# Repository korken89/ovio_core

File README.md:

# Open Visual Inertial Odometry (OVIO) Core

## Current status

Work in progress. PCB have arrived for v1.0 of the board and bring-up has started.

### Issues with v1.0 hardware (fixed in v1.1)

* The MOSFET is 180 degrees rotated.
* The MOSI/MISO lines for the SPI flash are swapped.
* The CS line of the SPI flash is connected to the wrong pad on the FPGA, flashing and loading bitstream from v1.0 hardware will not work.

Images from the assembly and results here: https://twitter.com/korken89/status/1341126909485342721

## Motivation

Aim: A "low cost" Visual Inertial Odometry accelerator.

A project to try out different vision processing pipelines, for Visual Inertial Odometry (VIO), on the ECP5 FPGA. As far as I know, the open hardware landscape of VIO cameras is slim to non-existent. Especially for systems which perform a majority of the pre-processing in the camera.

Things such as image convolutions, FAST corners, multi-scale images, non-maximum suppression, image gradients, etc, are extremely well suited for FPGA implementation.

Why do it on a PC? Let it run the actual Kalman Filter / MHE / nonlinear optimizer, which the FPGA is not well suited for.

## Specs

* Lattice ECP5U-85, design is pin-compatible to all the smaller versions
* 1 GBit DDR3 memory
* FT600 USB 3.0 FIFO with 200 MB/s transfer rate
* 2x MT9V034 cameras with tight hardware synchronization control loops (center of integration of both cameras are aligned to IMU measurements)
* Temperature stabilized ST ISM330DHC IMU (16g / 4000 dps max)

## Do you want one?

Previous projects has been made on Xilinx FPGAs, however the high cost of their FPGAs never allowed for trying to distribute a camera. Now it is expected that the hardware cost for this system should be sub 100 Euros, even with the largest ECP5 FPGA.

If there is interest for acquiring a camera, contact me (via any medium) and we'll figure something out.

## Lenses and lens holder

* http://www.m12lenses.com/2-1mm-F2-2-Board-Lens-p/pt-02120.htm
* http://www.m12lenses.com/M12-Lens-Holder-Plastic-p/pt-lh001p.htm

## Contributors

- Emil Fresk ([@korken89](https://github.com/korken89/))

## License

This hardware is open source.

TODO: Find a proper license

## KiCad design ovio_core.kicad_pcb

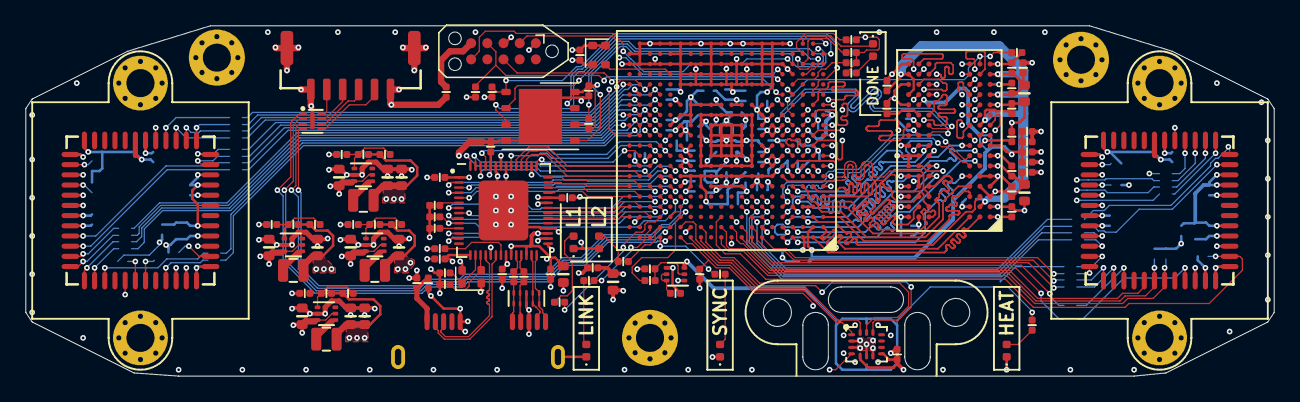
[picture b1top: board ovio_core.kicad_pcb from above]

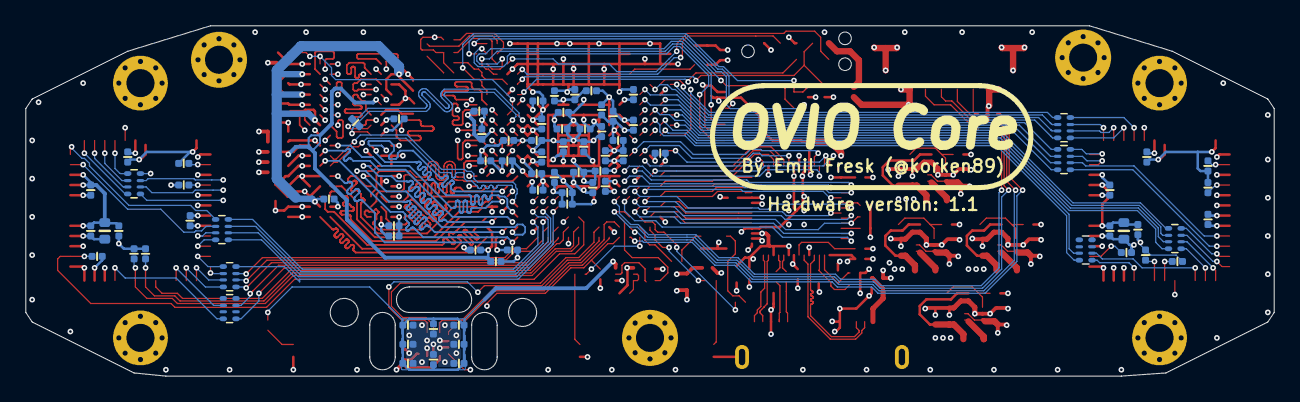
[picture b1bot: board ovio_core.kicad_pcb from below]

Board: 6 copper layers, 98.0 x 27.5 mm, 196 parts (81 on the bottom side), 224 nets.

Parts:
C101, C103, C210, C211, C214, C215, C218, C301, C303, C403, C404, C405, C406, C407, C408, C409, C410, C411, C412, C415, C416, C502, C601, C603, C605, C607, C608, C611, C612, C615, C616, C619, C620, C623, C624, C627, C701, C703, C705, C706, C707, C708, C709, C712, C713, C714, C715: 0.1u; C_0402
C102, C104, C212, C213, C216, C217, C219, C302, C413, C414, C418, C602, C604, C606, C609, C610, C617, C618, C621, C622, C625, C626, C628, C702, C704: 10n; C_0402
C201, C202, C203, C204, C401, C402, C501, C716: 4.7u; C_0603
C205, C206, C207, C208, C209, C220, C613, C614: 22u; C_0603
C221, C222, C223, C224, C710, C711: 10p; C_0402
D101, D102, D103, D104, D301, D501: LED_Small; LED_0402_1005Metric
FB401, FB402, FB501, FB601, FB602, FB701: Ferrite_Bead_Small; R_0402
H101, H102, H103: MountingHole_Pad; MountingHole_2.2mm_M2_Pad_Via
H501, H502: MountingHole; MountingHole_2.2mm_M2
J101: Conn_01x06; SM06B-GHS-TB
J301: TC2050; Tag-Connect_TC2050-IDC-NL_2x05_P1.27mm_Vertical
J701: USB3_B_Micro; AMPHENOL-GSB343K33HR
L201, L202, L203, L204: 2.2u; L_0806_2016Metric
LH401, LH402: lens_holder; m12_20mm
Q501: NTZD3155C; SOT-563
R101, R102, R103, R104, R301, R302, R303, R304, R306, R407, R408, R409, R410, R513, R601, R602: 1k; R_0402
R201, R204: 100k; R_0402
R202: 120k; R_0402
R203: 150k; R_0402
R205: 261k; R_0402
R206, R208: 82k; R_0402
R207: 365k; R_0402
R305, R307, R403, R404, R502, R503, R508, R604, R701, R702, R703: 10k; R_0402
R308: 0; R_0402
R401, R402, R405, R406, R704: 1.6k; R_0402
R501, R504, R505, R506, R507, R509, R510, R511, R512: 180; R_0402
R603: 100; R_0402
R605: 240; R_0402
RN401, RN402, RN403, RN404, RN406, RN407, RN408, RN409: 22; R_Array_Convex_4x0402
U101: IP4254CZ8-4-TTL; UDFN-8-1EP_1.7x1.35mm_P0.4mm_EP0.4x1.2mm
U102: ECP5U_85_CABGA381; caBGA_381_17x17
U201, U202, U203, U204: TLV62569DRL; SOT-563
U302: W25Q128JVP; WSON-8-1EP_6x5mm_P1.27mm_EP3.4x4.3mm
U401, U402: MT9V034
U403: 25 MHz; Crystal_4Pin_2.0x1.6mm
U501: ISM330DHC; LGA-14-2.5x3
U601: MT41J128M16JT-125:K; BGA-96_8.0x14.0mm_DDR16
U701: FT600Q; QFN-56-1EP_7x7mm_P0.4mm_EP5.7x5.7mm_FT600
U702: PUSB3FR4Z; DFN-10-1.0x2.5mm_P0.5mm
Y701: 30 MHz; Crystal_4Pin_2.0x1.6mm

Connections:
+1V1: C205.1, C209.1, C210.1, C212.1, C214.1, C216.1, C218.1, C219.1, C221.2, L201.2, R201.2, U102.H8, U102.H9, U102.H10, U102.H11, U102.H12, U102.H13, U102.J8, U102.J13, U102.K8, U102.K13, U102.L8, U102.L13, U102.M8, U102.M13, U102.N8, U102.N9, U102.N10, U102.N11, U102.N12, U102.N13
+1V5: C206.1, C222.2, C601.1, C602.1, C603.1, C604.1, C605.1, C606.1, C611.1, C627.1, C628.1, FB601.1, FB602.1, L202.2, R203.2, R601.1, U102.A3, U102.D2, U102.D3, U102.H3, U102.H6, U102.H7, U102.J5, U102.J6, U102.L3, U102.L6, U102.L7, U102.M5, U102.M6, U102.N1
+2V5: C207.1, C211.1, C213.1, C215.1, C217.1, C223.2, L203.2, R205.2, U102.F6, U102.F15, U102.P6, U102.P15
+3V3: C101.1, C102.1, C103.1, C104.1, C208.1, C220.1, C224.2, C301.1, C302.1, C303.1, C403.1, C405.1, C407.1, C409.1, C411.1, C412.1, C413.1, C414.1, C415.1, C416.1, C418.1, C701.1, C702.1, C703.1, C704.1, C706.1, C707.1, C708.1, C714.1, FB401.2, FB402.2, FB501.2, J301.1, L204.2, R207.2, R301.1, R302.1, R303.1, R304.1, R305.1, R307.1, R401.2, R402.2, R405.2, R406.2, R407.1, R408.1, R409.1, R410.1, R701.1, R702.1, R703.1, U102.F9, U102.F10, U102.F11, U102.F12, U102.H14, U102.H15, U102.J15, U102.J18, U102.L14, U102.L15, U102.M15, U102.P9, U102.P10, U302.8, U401.1, U401.6, U401.14, U401.28, U402.1, U402.6, U402.14, U402.28, U403.1, U403.4, U701.15, U701.19, U701.22, U701.30, U701.38, U701.44, U701.52
+5V: C201.1, C202.1, C203.1, C204.1, FB701.1, J101.1, Q501.4, R308.2, R503.1, U201.3, U201.5, U202.3, U202.5, U203.3, U203.5, U204.3, U204.5, U701.29
/2x cameras & FPGA Clock/CAM0_D0: RN402.7, U102.E8
/2x cameras & FPGA Clock/CAM0_D0_P: RN402.2, U401.45
/2x cameras & FPGA Clock/CAM0_D1: RN402.6, U102.E9
/2x cameras & FPGA Clock/CAM0_D1_P: RN402.3, U401.44
/2x cameras & FPGA Clock/CAM0_D2: RN402.5, U102.C10
/2x cameras & FPGA Clock/CAM0_D2_P: RN402.4, U401.43
/2x cameras & FPGA Clock/CAM0_D3: RN403.8, U102.C7
/2x cameras & FPGA Clock/CAM0_D3_P: RN403.1, U401.42
/2x cameras & FPGA Clock/CAM0_D4: RN403.7, U102.C8
/2x cameras & FPGA Clock/CAM0_D4_P: RN403.2, U401.41
/2x cameras & FPGA Clock/CAM0_D5: RN403.6, U102.D7
/2x cameras & FPGA Clock/CAM0_D5_P: RN403.3, U401.15
/2x cameras & FPGA Clock/CAM0_D6: RN403.5, U102.D8
/2x cameras & FPGA Clock/CAM0_D6_P: RN403.4, U401.16
/2x cameras & FPGA Clock/CAM0_D7: RN404.8, U102.D9
/2x cameras & FPGA Clock/CAM0_D7_P: RN404.1, U401.17
/2x cameras & FPGA Clock/CAM0_D8: RN404.7, U102.A7
/2x cameras & FPGA Clock/CAM0_D8_P: RN404.2, U401.18
/2x cameras & FPGA Clock/CAM0_D9: RN404.6, U102.B8
/2x cameras & FPGA Clock/CAM0_D9_P: RN404.3, U401.19
/2x cameras & FPGA Clock/CAM0_FLASH: RN401.1, U102.A9
/2x cameras & FPGA Clock/CAM0_FLASH_P: RN401.8, U401.27
/2x cameras & FPGA Clock/CAM0_FV: RN401.3, U102.B9
/2x cameras & FPGA Clock/CAM0_FV_P: RN401.6, U401.21
/2x cameras & FPGA Clock/CAM0_LV: RN404.5, U102.A8
/2x cameras & FPGA Clock/CAM0_LV_P: RN404.4, U401.20
/2x cameras & FPGA Clock/CAM0_PIXCLK: RN402.8, U102.A10
/2x cameras & FPGA Clock/CAM0_PIXCLK_P: RN402.1, U401.46
/2x cameras & FPGA Clock/CAM0_RESET: R403.1, U102.C11, U401.32
/2x cameras & FPGA Clock/CAM0_SCLK: R405.1, U102.A11, U401.25
/2x cameras & FPGA Clock/CAM0_SDATA: R401.1, U102.B11, U401.24
/2x cameras & FPGA Clock/CAM0_SYSCLK: U102.E7, U401.47
/2x cameras & FPGA Clock/CAM0_TRIGGER: U102.B10, U401.23
/2x cameras & FPGA Clock/CAM0_VAA: C401.1, C404.1, C408.1, FB401.1, U401.35, U401.39, U401.40
/2x cameras & FPGA Clock/CAM1_D0: RN407.8, U102.T18
/2x cameras & FPGA Clock/CAM1_D0_P: RN407.1, U402.45
/2x cameras & FPGA Clock/CAM1_D1: RN407.7, U102.T20
/2x cameras & FPGA Clock/CAM1_D1_P: RN407.2, U402.44
/2x cameras & FPGA Clock/CAM1_D2: RN407.6, U102.T19
/2x cameras & FPGA Clock/CAM1_D2_P: RN407.3, U402.43
/2x cameras & FPGA Clock/CAM1_D3: RN408.5, U102.R17
/2x cameras & FPGA Clock/CAM1_D3_P: RN408.4, U402.42
/2x cameras & FPGA Clock/CAM1_D4: RN408.6, U102.P19
/2x cameras & FPGA Clock/CAM1_D4_P: RN408.3, U402.41
/2x cameras & FPGA Clock/CAM1_D5: RN408.7, U102.P17
/2x cameras & FPGA Clock/CAM1_D5_P: RN408.2, U402.15
/2x cameras & FPGA Clock/CAM1_D6: RN408.8, U102.N19
/2x cameras & FPGA Clock/CAM1_D6_P: RN408.1, U402.16
/2x cameras & FPGA Clock/CAM1_D7: RN409.5, U102.N20
/2x cameras & FPGA Clock/CAM1_D7_P: RN409.4, U402.17
/2x cameras & FPGA Clock/CAM1_D8: RN409.6, U102.N18
/2x cameras & FPGA Clock/CAM1_D8_P: RN409.3, U402.18
/2x cameras & FPGA Clock/CAM1_D9: RN409.7, U102.M20
/2x cameras & FPGA Clock/CAM1_D9_P: RN409.2, U402.19
/2x cameras & FPGA Clock/CAM1_FLASH: RN406.4, U102.M18
/2x cameras & FPGA Clock/CAM1_FLASH_P: RN406.5, U402.27
/2x cameras & FPGA Clock/CAM1_FV: RN406.3, U102.L19
/2x cameras & FPGA Clock/CAM1_FV_P: RN406.6, U402.21
/2x cameras & FPGA Clock/CAM1_LV: RN409.8, U102.M19
/2x cameras & FPGA Clock/CAM1_LV_P: RN409.1, U402.20
/2x cameras & FPGA Clock/CAM1_PIXCLK: RN407.5, U102.L20
/2x cameras & FPGA Clock/CAM1_PIXCLK_P: RN407.4, U402.46
/2x cameras & FPGA Clock/CAM1_RESET: R404.1, U102.L17, U402.32
/2x cameras & FPGA Clock/CAM1_SCLK: R406.1, U102.L18, U402.25
/2x cameras & FPGA Clock/CAM1_SDATA: R402.1, U102.M17, U402.24
/2x cameras & FPGA Clock/CAM1_SYSCLK: U102.N17, U402.47
/2x cameras & FPGA Clock/CAM1_TRIGGER: U102.L16, U402.23
/2x cameras & FPGA Clock/CAM1_VAA: C402.1, C406.1, C410.1, FB402.1, U402.35, U402.39, U402.40
/2x cameras & FPGA Clock/CLOCK_PLL_IN: U102.U16, U403.3
/DDR3 Memory/A0: U102.K2, U601.N3
/DDR3 Memory/A1: U102.L4, U601.P7
/DDR3 Memory/A2: U102.L2, U601.P3
/DDR3 Memory/A3: U102.J1, U601.N2
/DDR3 Memory/A4: U102.N2, U601.P8
/DDR3 Memory/A5: U102.L1, U601.P2
/DDR3 Memory/A6: U102.P2, U601.R8
/DDR3 Memory/A7: U102.P1, U601.R2
/DDR3 Memory/A8: U102.M3, U601.T8
/DDR3 Memory/A9: U102.L5, U601.R3
/DDR3 Memory/A10: U102.K1, U601.L7
/DDR3 Memory/A11: U102.N3, U601.R7
/DDR3 Memory/A12: U102.K3, U601.N7
/DDR3 Memory/A13: U102.P5, U601.T3
/DDR3 Memory/BA0: U102.H1, U601.M2
/DDR3 Memory/BA1: U102.M1, U601.N8
/DDR3 Memory/BA2: U102.K4, U601.M3
/DDR3 Memory/CAS_N: U102.G1, U601.K3
/DDR3 Memory/CK_E: U102.J3, U601.K9
/DDR3 Memory/CK_N: R603.2, U102.N5, U601.K7
/DDR3 Memory/CK_P: R603.1, U102.M4, U601.J7
/DDR3 Memory/CS_N: U102.H2, U601.L2
/DDR3 Memory/DQ0: U102.A4, U601.E3
/DDR3 Memory/DQ1: U102.C3, U601.F7
/DDR3 Memory/DQ2: U102.A5, U601.F2
/DDR3 Memory/DQ3: U102.B5, U601.F8
/DDR3 Memory/DQ4: U102.E3, U601.H3
/DDR3 Memory/DQ5: U102.F4, U601.H8
/DDR3 Memory/DQ6: U102.C4, U601.G2
/DDR3 Memory/DQ7: U102.C5, U601.H7
/DDR3 Memory/DQ8: U102.D1, U601.D7
/DDR3 Memory/DQ9: U102.C1, U601.C3
/DDR3 Memory/DQ10: U102.F2, U601.C8
/DDR3 Memory/DQ11: U102.C2, U601.C2
/DDR3 Memory/DQ12: U102.E2, U601.A7
/DDR3 Memory/DQ13: U102.A2, U601.A2
/DDR3 Memory/DQ14: U102.E1, U601.B8
/DDR3 Memory/DQ15: U102.B1, U601.A3
/DDR3 Memory/DRAM_VDD: C613.1, C615.1, C617.1, C619.1, C621.1, C623.1, C625.1, FB601.2, U601.B2, U601.D9, U601.G7, U601.K2, U601.K8, U601.N1, U601.N9, U601.R1, U601.R9
/DDR3 Memory/DRAM_VDDQ: C614.1, C616.1, C618.1, C620.1, C622.1, C624.1, C626.1, FB602.2, U601.A1, U601.A8, U601.C1, U601.C9, U601.D2, U601.E9, U601.F1, U601.H2, U601.H9
/DDR3 Memory/LDM: U102.B4, U601.E7
/DDR3 Memory/LDQS_N: U102.D5, U601.G3
/DDR3 Memory/LDQS_P: U102.E4, U601.F3
/DDR3 Memory/ODT: U102.F1, U601.K1
/DDR3 Memory/RAS_N: U102.G2, U601.J3
/DDR3 Memory/RESET_N: R604.1, U102.N4, U601.T2
/DDR3 Memory/UDM: U102.F3, U601.D3
/DDR3 Memory/UDQS_N: U102.G5, U601.B7
/DDR3 Memory/UDQS_P: U102.H4, U601.C7
/DDR3 Memory/VREF: C607.1, C608.1, C609.1, C610.1, C611.2, C612.1, R601.2, R602.1, U102.B2, U102.K5, U601.H1, U601.M8
/DDR3 Memory/WE_N: U102.J4, U601.L3
/DDR3 Memory/ZQ: R605.1, U601.L8
/FPGA Config/CFG_1: R302.2, U102.T4
/FPGA Config/DONE: D301.1, U102.Y3
/FPGA Config/INITN: R305.2, U102.V3
/FPGA Config/PROGRAMN: R304.2, U102.W3
/FPGA Config/SPI_CLK: R301.2, U102.U3, U302.6
/FPGA Config/SPI_CS: R307.2, U102.R2, U302.1
/FPGA Config/SPI_D2: U102.Y2, U302.3
/FPGA Config/SPI_D3: U102.W1, U302.7
/FPGA Config/SPI_MISO: U102.V2, U302.2
/FPGA Config/SPI_MOSI: U102.W2, U302.5
/FPGA Config/TCK: J301.4, R306.1, U102.T5
/FPGA Config/TDI: J301.8, U102.R5
/FPGA Config/TDO: J301.6, U102.V4
/FPGA Config/TMS: J301.2, U102.U5
/Heated IMU/HEATER_BASE: Q501.5, Q501.6, R503.2
/Heated IMU/HEATER_SIG: Q501.2, R501.1, R502.1
/Heated IMU/IMU_HEATER: Q501.3, R504.1, R505.1, R506.1, R507.1, R509.1, R510.1, R511.1, R512.1, R513.1
/Heated IMU/IMU_PWR: C501.1, C502.1, FB501.1, U501.5, U501.8
/IMU_CS: U102.A13, U501.12
/IMU_HEATER: R501.2, U102.C15
/IMU_INT: R508.1, U102.A15, U501.4
/IMU_SCK: U102.B13, U501.13
/IMU_SDI: U102.B15, U501.14
/IMU_SDO: U102.A14, U501.1
/LED1: R101.1, U102.B17
/LED2: R102.1, U102.C17
/LED3: R103.1, U102.A17
/LED4: R104.1, U102.B18
/P_USER_FLASH_OUT: U101.4, U102.E15
/P_USER_GPIO0: U101.1, U102.A16
/P_USER_GPIO1: U101.2, U102.B16
/P_USER_GPIO2: U101.3, U102.C16
/System Power/FB_1V1: C221.1, R201.1, R202.2, U201.1
/System Power/FB_1V5: C222.1, R203.1, R204.2, U202.1
/System Power/FB_2V5: C223.1, R205.1, R206.2, U203.1
/System Power/FB_3V3: C224.1, R207.1, R208.2, U204.1
/USB FIFO Interface/D_N: J701.2, U701.20
/USB FIFO Interface/D_P: J701.3, U701.18
/USB FIFO Interface/FT_BE0: U102.H17, U701.2
/USB FIFO Interface/FT_BE1: U102.G16, U701.3
/USB FIFO Interface/FT_CLKOUT: U102.J19, U701.43
/USB FIFO Interface/FT_D0: U102.C20, U701.33
/USB FIFO Interface/FT_D1: U102.C18, U701.34
/USB FIFO Interface/FT_D2: U102.D20, U701.35
/USB FIFO Interface/FT_D3: U102.D19, U701.36
/USB FIFO Interface/FT_D4: U102.E20, U701.39
/USB FIFO Interface/FT_D5: U102.E19, U701.40
/USB FIFO Interface/FT_D6: U102.F20, U701.41
/USB FIFO Interface/FT_D7: U102.F19, U701.42
/USB FIFO Interface/FT_D8: U102.G20, U701.45
/USB FIFO Interface/FT_D9: U102.G19, U701.46
/USB FIFO Interface/FT_D10: U102.H20, U701.47
/USB FIFO Interface/FT_D11: U102.J17, U701.48
/USB FIFO Interface/FT_D12: U102.J16, U701.53
/USB FIFO Interface/FT_D13: U102.H16, U701.54
/USB FIFO Interface/FT_D14: U102.H18, U701.55
/USB FIFO Interface/FT_D15: U102.G18, U701.56
/USB FIFO Interface/FT_GPIO0: U102.D17, U701.12
/USB FIFO Interface/FT_GPIO1: U102.E16, U701.13
/USB FIFO Interface/FT_REF: R704.1, U701.21
/USB FIFO Interface/FT_WAKEUP: R701.2, U701.11
/USB FIFO Interface/RX_N: J701.9, U701.27, U702.4, U702.7
/USB FIFO Interface/RX_P: J701.10, U701.28, U702.5, U702.6
/USB FIFO Interface/TX_N: C712.1, J701.6, U702.1, U702.10
/USB FIFO Interface/TX_P: C713.1, J701.7, U702.2, U702.9
/USB FIFO Interface/TX_P_N: C712.2, U701.24
/USB FIFO Interface/TX_P_P: C713.2, U701.25
/USB FIFO Interface/VBUS_IN: C705.1, FB701.2, J701.1
/USB FIFO Interface/~FT_OE: U102.E17, U701.9
/USB FIFO Interface/~FT_RD: U102.E18, U701.8
/USB FIFO Interface/~FT_RESET: R702.2, U102.D18, U701.10
/USB FIFO Interface/~FT_RXF: U102.F18, U701.5
/USB FIFO Interface/~FT_SIWU: R703.2, U701.6
/USB FIFO Interface/~FT_TXE: U102.F16, U701.4
/USB FIFO Interface/~FT_WR: U102.F17, U701.7
/USER_FLASH_OUT: J101.2, U101.5
/USER_GPIO0: J101.5, U101.8
/USER_GPIO1: J101.4, U101.7
/USER_GPIO2: J101.3, U101.6
GND: C101.2, C102.2, C103.2, C104.2, C201.2, C202.2, C203.2, C204.2, C205.2, C206.2, C207.2, C208.2, C209.2, C210.2, C211.2, C212.2, C213.2, C214.2, C215.2, C216.2, C217.2, C218.2, C219.2, C220.2, C301.2, C302.2, C303.2, C401.2, C402.2, C403.2, C404.2, C405.2, C406.2, C407.2, C408.2, C409.2, C410.2, C411.2, C412.2, C413.2, C414.2, C415.2, C416.2, C418.2, C501.2, C502.2, C601.2, C602.2, C603.2, C604.2, C605.2, C606.2, C607.2, C608.2, C609.2, C610.2, C612.2, C613.2, C614.2, C615.2, C616.2, C617.2, C618.2, C619.2, C620.2, C621.2, C622.2, C623.2, C624.2, C625.2, C626.2, C627.2, C628.2, C701.2, C702.2, C703.2, C704.2, C705.2, C706.2, C707.2, C708.2, C709.2, C710.2, C711.2, C714.2, C715.2, C716.2, D101.1, D102.1, D103.1, D104.1, D501.1, H101.1, H102.1, H103.1, J101.0, J101.6, J301.3, J701.5, J701.8, J701.11, LH401.1, LH401.2, LH402.1, LH402.2, Q501.1, R202.1, R204.1, R206.1, R208.1, R306.2, R403.2, R404.2, R502.2, R504.2, R505.2, R506.2, R507.2, R508.2, R509.2, R510.2, R511.2, R512.2, R602.2, R604.2, R605.2, R704.2, U101.9, U102.B7, U102.B14, U102.C19, U102.D4, U102.F7, U102.F8, U102.F13, U102.F14, U102.G4, U102.G6, U102.G7, U102.G8, U102.G9, U102.G10, U102.G11, U102.G12, U102.G13, U102.G14, U102.G15, U102.G17, U102.H19, U102.J2, U102.J7, U102.J9, U102.J10, U102.J11, U102.J12, U102.J14, U102.K6, U102.K7, U102.K9, U102.K10, U102.K11, U102.K12, U102.K14, U102.K15, U102.L9, U102.L10, U102.L11, U102.L12, U102.M2, U102.M7, U102.M9, U102.M10, U102.M11, U102.M12, U102.M14, U102.M16, U102.N6, U102.N7, U102.N14, U102.N15, U102.P7, U102.P8, U102.P11, U102.P12, U102.P13, U102.P14, U102.R4, U102.R19, U102.T6, U102.T7, U102.T8, U102.T9, U102.T10, U102.T11, U102.T12, U102.T13, U102.T14, U102.T15, U102.U4, U102.U6, U102.U7, U102.U8, U102.U9, U102.U10, U102.U11, U102.U12, U102.U13, U102.U14, U102.U15, U102.V5, U102.V6, U102.V7, U102.V8, U102.V9, U102.V10, U102.V11, U102.V12, U102.V13, U102.V14, U102.V15, U102.V16, U102.V17, U102.V18, U102.V19, U102.V20, U102.W6, U102.W7, U102.W12, U102.W15, U102.W16, U102.W19, U102.W20, U102.Y5, U102.Y6, U102.Y7, U102.Y8, U102.Y11, U102.Y12, U102.Y14, U102.Y15, U102.Y16, U102.Y17, U102.Y19, U201.2, U202.2, U203.2, U204.2, U302.4, U302.9, U401.7, U401.9, U401.11, U401.12, U401.13, U401.29, U401.30, U401.31, U401.33, U401.34, U401.38, U401.48, U402.7, U402.9, U402.11, U402.12, U402.13, U402.29, U402.30, U402.31, U402.33, U402.34, U402.38, U402.48, U403.2, U501.2, U501.3, U501.6, U501.7, U601.A9, U601.B1, U601.B3, U601.B9, U601.D1, U601.D8, U601.E1, U601.E2, U601.E8, U601.F9, U601.G1, U601.G8, U601.G9, U601.J2, U601.J8, U601.M1, U601.M9, U601.P1, U601.P9, U601.T1, U601.T9, U701.32, U701.49, U701.51, U701.57, U702.3, U702.8, Y701.2, Y701.4
unnamed: C710.1, U701.16, Y701.1
unnamed: C711.1, U701.17, Y701.3
unnamed: D101.2, R101.2
unnamed: D102.2, R102.2
unnamed: D103.2, R103.2
unnamed: D104.2, R104.2
unnamed: D301.2, R303.2
unnamed: D501.2, R513.2
unnamed: J301.5, R308.1
unnamed: L201.1, U201.4
unnamed: L202.1, U202.4
unnamed: L203.1, U203.4
unnamed: L204.1, U204.4
unnamed: R407.2, U401.8
unnamed: R408.2, U402.8
unnamed: R409.2, U401.10
unnamed: R410.2, U402.10
VD10: C709.1, C715.1, C716.1, U701.1, U701.23, U701.26, U701.31, U701.37, U701.50

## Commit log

2020-11-15 Schematic, general layout and DDR3 routing done
2020-11-15 USB 3.0 chip layout
2020-11-16 Fixed libs
2020-11-16 USB fifo routed
2020-11-16 More routing
2020-11-22 Camera 1, JTAG, SPI Flash routed
2020-11-23 DRC pass, routing finished
2020-11-24 Added comments and fixed ERC erros
2020-11-24 Added info to sheets, added hardware version to board
2020-11-24 Minor skew fix on HS USB lines
2020-11-24 Minor fixes
2020-11-28 Now with TC2050 for programming
2020-11-28 Small cleanup for PCB order
2020-12-22 Updated from v1.0 build
